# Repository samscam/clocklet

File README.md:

# Clocklet

See also [clocklet.co.uk](https://clocklet.co.uk)

## Overview

This project is the firmware and client apps for clocks made by @samscam including:

### Clocklet
* Custom 17x5 SK9822 LED Matrix display
* Timekeeping: ESP32 (DS3231 as backup)
* Synchronisation: NTP
* Microcontroller: ESP32 Wrover on custom "Clockbrain" board
* Weather source: OpenWeatherMap

### Old Clocklet / Clocky
Earlier prototypes used RGBDigit (WS2812B) 7-segment display and Adafruit Feather Huzzah32.

### Mrs Clockety
* Display: Waveshare epaper 2.9inch https://www.waveshare.com/2.9inch-e-paper-module.htm
* Timekeeping: GPS
* Synchronisation: GPS
* Power management to run from a lipo battery
* Microcontroller: Adafruit Feather Huzzah32

It's all a work in progress.

## Main Features

* Time
* Weather
* Utterances
* Interesing displays and animation
* Ambient light sensing
* Power management (Mrs Clockety)

## Firmware

To build the the firmware:

* Clone the repo **including submodules**
* Install platformio and your editor of choice - I'm using vscode.
* Open up the firmware from the `Embedded` directory
* Pick the *correct environment* for the device you want to build for (by setting it in the first line of `platformio.ini` or by invoking tasks for the specific environment in the editor/cli) this will probably be `clockbrain`
* Plug the device in to your machine over USB
* Check that the device is available to your system... on MacOS it's normally `/dev/cu.SLAB_USBtoUART`
* Build and upload (platformio should download the dependencies if it hasn't done so already)
* Note that API keys are encrypted with gitcrypt

## Seeing the logs (without installing anything much)

You can connect to the clocklet's serial port from a computer with various tools (like screen, miniterm or putty) and see the Clocklet logging.

The important thing to note is that the baud rate of the serial connection is `115200`.

The Clocklet serial port on Mac and Linux will be available as something like `/dev/cu.SLAB_USBtoUART` - you can do an `ls /dev/cu.*` before and after plugging it in to eliminate possibilities.

Then open it up in your tool of choice:
`screen /dev/cu.SLAB_USBtoUART 115200`
`miniterm.py /dev/cu.SLAB_USBtoUART 115200`

## Manually updating firmware (with minimal installing)

1) Install `esptool`

On MacOS this can be done with homebrew: `brew install esptool`
On Linuxes it's probably available from `apt install esptool` or whatever package manager you're using.

2) Download the bin file of the firmware image you want from the releases section on here.

3) Plug in the Clocklet and figure out which port it is on - probably something like `/dev/cu.SLAB_USBtoUART` (that's what we'll use here but replace with whatever it is on your system)

4) Erase the flash (including settings)
`esptool.py -b 115200 -p /dev/cu.SLAB_USBtoUART erase_region 0x9000 0xFF7000`

5) Flash the new firmware image:

`esptool.py -b 115200 -p /dev/cu.SLAB_USBtoUART write_flash 0x10000 clockbrain.bin`

While we are here you can also use esptool to just erase settings (equivalent of doing a factory reset from the app): 
`esptool.py -b 115200 -p /dev/cu.SLAB_USBtoUART erase_region 0x9000 0x5000`

## Client App (iOS)

*Requires Xcode 16*
To build, open via the workspace rather than the Xcode Project.

Contains an experimental library for gluing CoreBluetooth to Combine and SwiftUI via PropertyWrappers called "CombineBluetooth". This may get spun out into a separate project in the future - but for ease of development right now it's in here.

## To follow

* Android client
* Enclosure design (3d printable)
* Hardware design

## License

This is distributed under the MIT License

    MIT License

    Copyright (c) 2017-2020 Sam Easterby-Smith

    Permission is hereby granted, free of charge, to any person obtaining a copy
    of this software and associated documentation files (the "Software"), to deal
    in the Software without restriction, including without limitation the rights
    to use, copy, modify, merge, publish, distribute, sublicense, and/or sell
    copies of the Software, and to permit persons to whom the Software is
    furnished to do so, subject to the following conditions:

    The above copyright notice and this permission notice shall be included in all
    copies or substantial portions of the Software.

    THE SOFTWARE IS PROVIDED "AS IS", WITHOUT WARRANTY OF ANY KIND, EXPRESS OR
    IMPLIED, INCLUDING BUT NOT LIMITED TO THE WARRANTIES OF MERCHANTABILITY,
    FITNESS FOR A PARTICULAR PURPOSE AND NONINFRINGEMENT. IN NO EVENT SHALL THE
    AUTHORS OR COPYRIGHT HOLDERS BE LIABLE FOR ANY CLAIM, DAMAGES OR OTHER
    LIABILITY, WHETHER IN AN ACTION OF CONTRACT, TORT OR OTHERWISE, ARISING FROM,
    OUT OF OR IN CONNECTION WITH THE SOFTWARE OR THE USE OR OTHER DEALINGS IN THE
    SOFTWARE.

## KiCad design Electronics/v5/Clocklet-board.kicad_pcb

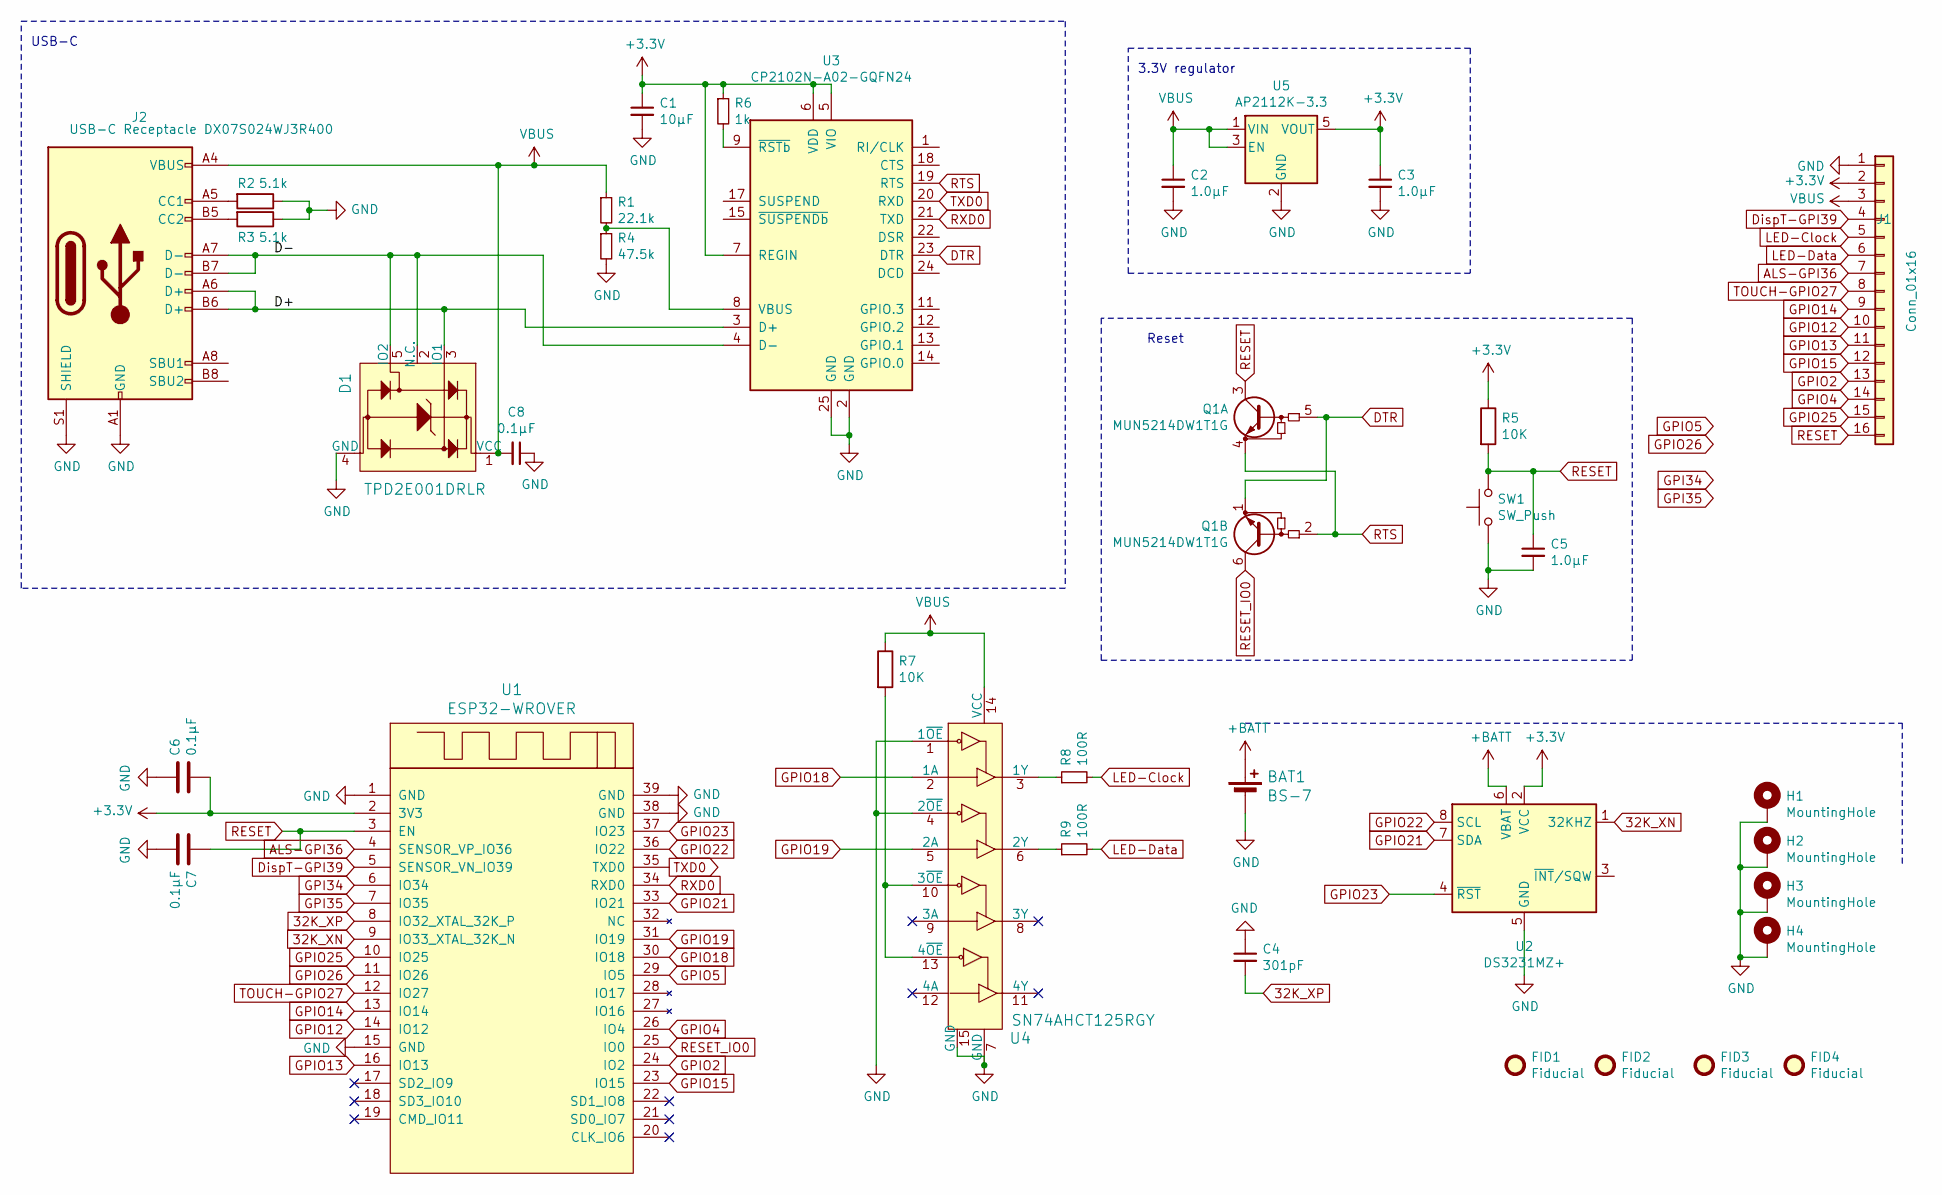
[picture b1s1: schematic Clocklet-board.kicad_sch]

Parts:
BAT1: BS-7; BatteryHolder_Keystone_3000_1x12mm; MPN BS-7; Digi-Key_PN BS-7-ND
C1: 10µF; C_0603_1608Metric; Mouser Ref 80-C0603C106M8PACTU
C2, C3, C5: 1.0µF; C_0603_1608Metric; Mouser Ref 80-C0603C105K4PLR
C4: 301pF; C_0603_1608Metric; Mouser Ref 80-C0603C301J8HACTU
C6, C7, C8: 0.1µF; C_0603_1608Metric; Mouser Ref 710-885012206071
D1: TPD2E001DRLR; SOT-553; MPN TPD2E001DRLR; Digi-Key_PN 296-21883-1-ND
FID1, FID2, FID3, FID4: Fiducial; Fiducial_0.5mm_Mask1mm
H1: MountingHole; MountingHole_2.7mm_M2.5_Pad_Via
H2, H3, H4: MountingHole; MountingHole_2.5mm_Pad_Via
J1: Conn_01x16; PinHeader_1x16_P2.54mm_Vertical
J2: USB-C Receptacle DX07S024WJ3R400; USB-C_Female_Vert_DX07S024WJ3R400-Corrected; Mouser Ref 656-DX07S0024WJ3R400
Q1: MUN5214DW1T1G; SOT-363_SC-70-6; Mouser Ref 863-MUN5214DW1T1G
R1: 22.1k; R_0603_1608Metric; Mouser Ref 71-CRCW060322K1FKEAC
R2, R3: 5.1k; R_0603_1608Metric; Mouser Ref 71-CRCW06035K10FKEAC
R4: 47.5k; R_0603_1608Metric; Mouser Ref 71-CRCW060347K5FKEAC
R5, R7: 10K; R_0603_1608Metric; Mouser Ref 71-CRCW060310K0FKEAC
R6: 1k; R_0603_1608Metric; Mouser Ref 71-CRCW06031K00FKEAC
R8, R9: 100R; R_0603_1608Metric; Mouser Ref 71-CRCW0603100RFKEAC
SW1: SW_Push; SW_SPST_B3U-1000P; Mouser Ref 653-B3U-1000P
U1: ESP32-WROVER; ESP32-WROVER-B-Recs; Mouser Ref 356-ESP32-WROB(16MB)
U2: DS3231MZ+; SOIC-8_3.9x4.9mm_P1.27mm; Mouser Ref 700-DS3231MZ+
U3: CP2102N-A02-GQFN24; QFN-24-1EP_4x4mm_P0.5mm_EP2.6x2.6mm_ThermalVias; Mouser Ref 634-CP2102NA02GQFN24
U4: SN74AHCT125RGY; Texas_S-PVQFN-N14_ThermalVias; MPN SN74AHCT125N; Digi-Key_PN 296-4655-5-ND
U5: AP2112K-3.3; SOT-23-5; Mouser Ref 621-AP2112K-3.3TRG1

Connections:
32K_XN: U1.9 (IO33_XTAL_32K_N), U2.1 (32KHZ)
32K_XP: C4.2, U1.8 (IO32_XTAL_32K_P)
+3V3: C1.1, C3.1, C6.2, J1.2, R5.1, R6.1, U1.2 (3V3), U2.2 (VCC), U3.5 (VIO), U3.6 (VDD), U3.7 (REGIN), U5.5 (VOUT)
+BATT: BAT1.1 (+), U2.6 (VBAT)
/D+: D1.3 (IO1), J2.A6 (D+), J2.B6 (D+), U3.3 (D+)
/D-: D1.2 (N.C.), D1.5 (IO2), J2.A7 (D-), J2.B7 (D-), U3.4 (D-)
ALS-GPI36: J1.7, U1.4 (SENSOR_VP_IO36)
DTR: Q1.1 (E1), Q1.5 (B1), U3.23 (DTR)
DispT-GPI39: J1.4, U1.5 (SENSOR_VN_IO39)
GND: BAT1.2 (-), C1.2, C2.2, C3.2, C4.1, C5.2, C6.1, C7.2, C8.1, D1.4 (GND), H1.1, H2.1, H3.1, H4.1, J1.1, J2.A1 (GND), J2.A12 (GND), J2.B1 (GND), J2.B12 (GND), J2.S1 (SHIELD), R2.1, R3.1, R4.2, SW1.1, U1.1 (GND), U1.15 (GND), U1.38 (GND), U1.39 (GND), U2.5 (GND), U3.2 (GND), U3.25 (GND), U4.1 (1~OE), U4.4 (2~OE), U4.7 (GND), U4.15 (GND), U5.2 (GND)
GPI34: U1.6 (IO34)
GPI35: U1.7 (IO35)
GPIO2: J1.13, U1.24 (IO2)
GPIO4: J1.14, U1.26 (IO4)
GPIO5: U1.29 (IO5)
GPIO12: J1.10, U1.14 (IO12)
GPIO13: J1.11, U1.16 (IO13)
GPIO14: J1.9, U1.13 (IO14)
GPIO15: J1.12, U1.23 (IO15)
GPIO18: U1.30 (IO18), U4.2 (1A)
GPIO19: U1.31 (IO19), U4.5 (2A)
GPIO21: U1.33 (IO21), U2.7 (SDA)
GPIO22: U1.36 (IO22), U2.8 (SCL)
GPIO23: U1.37 (IO23), U2.4 (~RST)
GPIO25: J1.15, U1.10 (IO25)
GPIO26: U1.11 (IO26)
LED-Clock: J1.5, R8.2
LED-Data: J1.6, R9.2
unnamed: J2.A5 (CC1), R2.2
unnamed: J2.B5 (CC2), R3.2
unnamed: R1.2, R4.1, U3.8 (VBUS)
unnamed: R6.2, U3.9 (~RSTb)
unnamed: R7.2, U4.10 (3~OE), U4.13 (4~OE)
unnamed: R8.1, U4.3 (1Y)
unnamed: R9.1, U4.6 (2Y)
RESET: C5.1, C7.1, J1.16, Q1.3 (C1), R5.2, SW1.2, U1.3 (EN)
RESET_IO0: Q1.6 (C1), U1.25 (IO0)
RTS: Q1.2 (B1), Q1.4 (E1), U3.19 (RTS)
RXD0: U1.34 (RXD0), U3.21 (TXD)
TOUCH-GPIO27: J1.8, U1.12 (IO27)
TXD0: U1.35 (TXD0), U3.20 (RXD)
VBUS: C2.1, C8.2, D1.1 (VCC), J1.3, J2.A4 (VBUS), J2.A9 (VBUS), J2.B4 (VBUS), J2.B9 (VBUS), R1.1, R7.1, U4.14 (VCC), U5.1 (VIN), U5.3 (EN)

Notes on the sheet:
3.3V regulator
Reset
USB-C

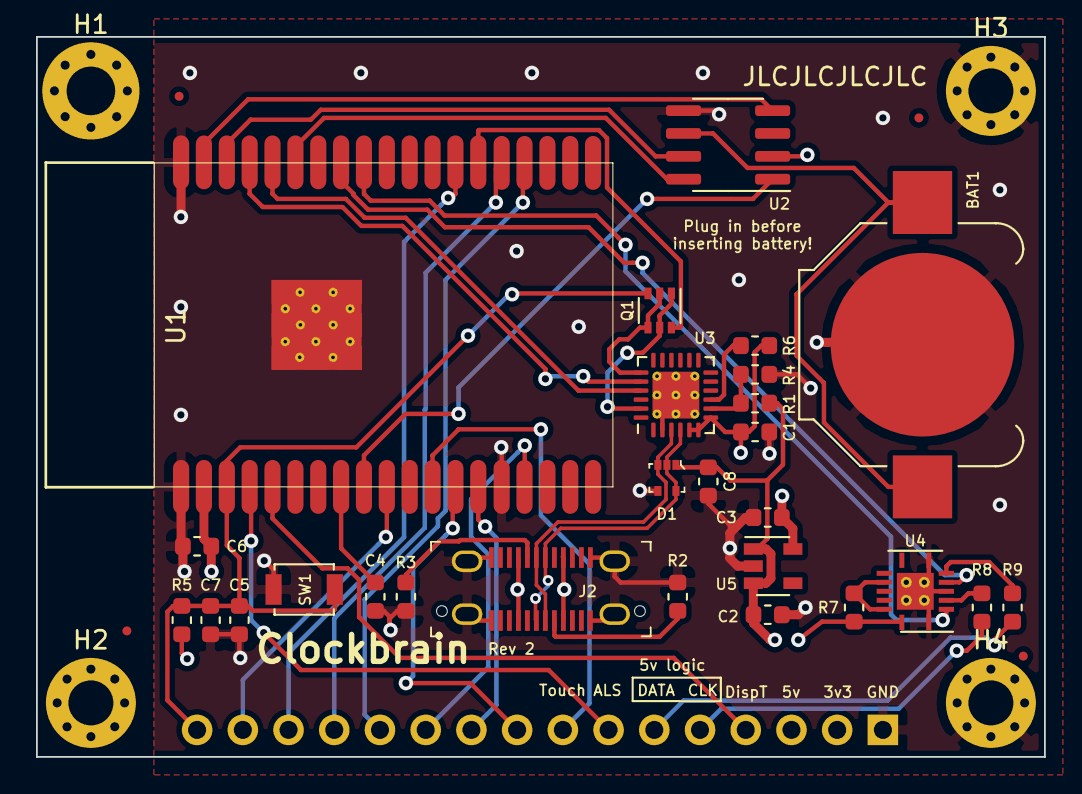
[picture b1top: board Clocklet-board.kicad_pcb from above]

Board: 4 copper layers, 56.0 x 40.0 mm, 36 parts (1 on the bottom side), 38 nets.

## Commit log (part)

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2020-07-11 Force reconnect attempt before running network calls
2020-07-11 Perform a network scan once, on creation of the BTNetworkService
2020-07-11 Adjusted some logging
2020-07-11 Set the partition table for new clocklets
2020-07-11 Only perform network scan on connect rather than at init
2020-07-12 Build both versions at the same time
2020-07-12 Say "WAIT" in capitals
2020-07-14 Matrix - logging using ESP_LOG
2020-07-16 Performed xcode's desired upgrade thing
2020-07-16 Disconnect devices on backgrounding and exit
2020-07-16 Made ConnectionState conform to equatable
2020-07-16 Various visual changes to the main list and detail views
2020-07-17 Just clockbrain while developing
2020-07-17 Added a reset handler to the BTPreferences Service
2020-07-17 Separated BT location service
2020-07-19 Bluetooth advertising - manufacturer data contains hwrev, case colour, serial
2020-07-20 Verbose logging corrections
2020-07-20 Pass locationManager to bluestuff on feathers
2020-07-20 Add a tiny delay between update jobs
2020-07-23 Updated dates and name in LICENSE
2020-07-23 No, don't free the bluetooth device name or you end up with garbage
2020-07-23 Added "configured" property to current location json structure
2020-07-23 Some stylistic movement of char *
2020-07-23 Removed some logging
2020-07-23 Faster startup. Run bluetooth setup sooner and synchronously on core 1
2020-07-24 Corrected some logging in the network status changes
2020-07-24 Inconsequential syntax changes
2020-07-24 Prevent landscape orientation
2020-07-24 Added ability to switch time styles
2020-07-25 Switched back to a viewmodel for networkSummaryView
2020-07-25 Whole bunch of stuff to make CombineBluetooth a bit tidier
2020-07-25 Started tightening up some of the internals of CombineBluetooth
2020-07-25 Removed logging
2020-07-25 Fixed misreporting of pref values over bluetooth
2020-07-26 Changed default value for timeStyle
2020-07-27 Expose bluetooth state to user in the clocklist if it's not right
2020-07-27 Overhaul of how CombineBluetooth conforms to ObservableObject - mostly to support mocking
2020-07-27 Some further layout improvements
2020-07-27 Disable location proxy after one result (because the documentation lies)
2020-07-28 Autoversioning wasn't applied right
2020-07-29 Added gold case colour as number 6
2020-07-29 Added NSBluetoothAlwaysUsageDescription
2020-07-29 Hide the not-got-a-clocklet button if you've got a clocklet
2020-07-30 Boolean (as one byte) characteristics
2020-07-30 Toggle for staging mode
2020-07-30 Improved negative space and layout
2020-07-30 Disabled autocorrection and autocapitalization in the password text field
2020-07-30 Show the git hash in the version info (on serial and over bluetooth)
2020-07-30 Wifi scan characteristic delivers results one-at-a-time
2020-07-31 Put the update scheduler on core 1 - hopefully more reliable
2020-07-31 Disable firmware updates if switched off in preferences
2020-07-31 Removed unused task machinery from BlueStuff
2020-08-01 Remove "wonky" time style from mock clock
2020-08-01 Added rough LocationDetailsView
2020-08-01 Rainbow logging ESP style
2020-08-01 Prep for release 0.0.9
2020-08-01 Significantly upped ram for firmware update response parsing
2020-08-03 Just checking semver stuff
2020-08-03 Sed recipe for getting versions including betas from git
2020-08-03 Brains, brains
2020-08-04 Removed SSL cert verification from Darksky because it was running out of ram and causing problems
2020-08-04 Removed code for adding a custom Generic Attribute Service 0x1801 because it was making things worse
2020-08-04 Switch on notifications within the network service when needed
2020-08-04 Force refresh of advertising data after a disconnect
2020-08-04 Renamed CurrentLocation to ClockLocation
2020-08-04 Moved TechnicalService to the start of the list - because it's less likely to change than the others now
2020-08-05 TIME ZONES
2020-08-05 Removed the periodic force-reconnect when bluetooth is connected but not scanning
2020-08-05 Whitespace
2020-08-06 Default timezone as Europe/London
2020-08-06 Half-implemented partial reset
2020-08-06 Added BluetoothOverlayView for when bluetooth is off or unauthorised or whatever
2020-08-06 LocationDetails has some more sample places including ones with funny timezones
2020-08-06 Always white text on the RoundyButtons
2020-08-06 Info.plist changes
2020-08-11 Corrected bluetooth start/stop for feather-based clocklets
2020-08-11 Better decimal time and blue status shown on display
2020-08-11 Empty virtual function for decimal time not breaking on rgbdigit
2020-08-11 Added releasse notes
2020-08-11 Gradually bumping the number on the efuse
2020-08-16 Case insensitive thunder for darksky
2020-08-16 Minor additions to deployment procedure
2020-08-17 Allow connections to open networks
2020-08-23 Brightness glue is now a float
2020-08-23 Re-enabled snow
2020-08-24 joinNetwork() method doesn't need to throw
2020-08-24 Upped max and min brightness for matrix display
2020-08-26 Colour correction
2020-08-26 Removed unused fetching of serial number
2020-08-26 Supress utterances while connected over bluetooth
2020-08-26 Added brightness setting
2020-08-30 Added autoBrightness toggle
2020-08-30 Yet another attempt at sorting out BLE advertising
2020-08-30 Fall back to ios13 style map - because it works properly
2020-08-30 Show a little message if the brightness setting is missing
2020-08-30 Slight code cleanup
2020-08-31 Added MapKit and CoreLocation into the project frameworks list
2020-09-01 Inconsequential change
2020-09-02 Catch unknown wifi statuses
2020-09-02 Added nimble-arduino
2020-09-03 nimble-arduino v1.0.1
2020-09-04 Made isValidLocation a method rather than a loose function
2020-09-04 Enable blutooth at boot on feathers!
2020-09-04 Fix sticky autoBrightness switch
2020-09-08 A bit of love for RGBDigit
2020-09-08 Moved submodules
2020-09-08 Say that it requires xcode 12
2020-09-08 Refactored Location to ClockLocation to avoid collision with SolTrack
2020-09-08 Return platformio settings to what they should be
2020-09-08 Efuse for clocklet 12
2020-09-08 Rainbows: Corrected troubles with not being near the prime meridian
2020-09-08 Force the app version to be 1.0 to avoid testflight reviews
    Fixes #36
2020-09-09 Removed telltale
    Closes #37
2020-09-09 Removed forcing of rainbows
2020-09-09 Second try at autoassign automation
2020-09-10 Fixed obviously mangled logging when ip address is updated
2020-09-12 Fixed mangled logging on discovering access points #48
2020-09-12 Do not include hidden SSIDs in scan results #50
2020-09-12 Some protection for over-subscription to scan and networkstatus #48
2020-09-12 Removed unused "Credentials.h"
2020-09-12 Corrected url in the board definition file
2020-09-12 Longer delay between wifi scans
2020-09-12 Adjusted heading styles in readme
2020-09-13 Dumbass: was passing a null pointer to the networkScanTask
2020-09-13 Both envs for release
2020-09-27 Add alert to confirm factory resets
    Closes #51
2020-09-27 Improved layout and display of network settings
2020-10-01 Indenting
2020-10-01 SPECIAL BOB VERSION
2020-11-30 Oh fun with serial ports
2020-11-30 Messing with shadows on renders
2021-11-14 ini and config changes
2021-11-15 Updated Semver library
2022-02-10 Wildcard serial port for platformio upload/monitor
2022-09-18 Project file update
2022-09-18 Details view: refactored to use newer syntax
2022-09-18 Attempt to do certificate pinning
2022-09-18 Fixed broken toggle switches and pickers
2022-10-01 Further modernisation of swiftui syntax
2022-10-01 Some improvements to UI previews
2022-10-01 Added disclosure chevron to ConfigItemView and improved hit area
2022-10-01 Use the SwiftUI Map view instead of MKMapView
2022-10-01 Better scaling of wifi strength to SFSymbols icon
2022-10-01 Revert "Use the SwiftUI Map view instead of MKMapView"
    This reverts commit 00a87dcab63da643c20c2163c2968a3af660afee.
2022-10-01 Removed deprecated animations
2022-10-02 Playing with animations on the searching eye
2022-10-07 Updated libraries, fixed code regressions
2022-10-07 Moved nimble-arduino from submodule to platformio dependency
2022-10-07 Fixed glue tags (again)
2022-10-09 Added api key for OpenWeatherMap
2022-10-09 Blatant obvious fail to allocate memory for a URL
2022-10-09 Switch current weather client to OWM
2022-11-02 Change to use x509 certificate bundle instead of pinning
2022-12-06 Fixed serialising of location and network service bluetooth payloads using std::string
2022-12-06 More detail when logging memory usage
2022-12-06 Create and delete preferences within FirmwareUpdates
2022-12-06 Removed weather summary as it was crashy
2022-12-06 Added ability to test forced firmware update
2022-12-06 Removed sloppy redirect handling as it’s now done by the library
2022-12-06 Fixed the Chatham Island time glitch
2022-12-08 iOS: fixed animation when connecting
2022-12-08 iOS: Fancier buttons
2022-12-08 iOS: factory reset button looked stupid
2022-12-08 iOS: Slightly larger icons for configItems
2022-12-09 iOS: Removed unnecessary logging when doing data conversions
2022-12-09 iOS: Renamed ClockConfigurator to ClockConfiguratorView
2022-12-09 iOS: Oh my! No more AppDelegate
2022-12-09 Embedded: only fetch ONE result when getting staging updates
2022-12-10 Embedded: further fixing of snow and drizzle
2022-12-10 Embedded: Added drizzle to display tests
2022-12-10 Embedded: Brought back frost
2022-12-10 Embedded: Moved all the Matrix display files into a directory together
2022-12-16 Embedded: Weird fun with memory leaks
2022-12-16 Embedded: Less new and delete when constructing httpclients
2022-12-17 Embedded: Added force update to gatt - when changing bluetooth services/chars
2022-12-20 Embedded: Changed matrix display to use precip intensity rather than probability
2022-12-20 iOS: Tidied up changes in Characteristic.swift
2022-12-20 Embedded: God mode service
2022-12-28 iOS: Reworked ClockList and root navigation
2022-12-30 iOS: Some refactoring of Bluetooth Overlay … kinda fixes #47 but still could be better
2022-12-30 Embedded: Changed bluetooth callbacks to try negotiating MTU
2022-12-30 Embedded: Removed some unused defines
2022-12-31 Embedded: Removed a leaky leaky leak
2022-12-31 Embedded: Added content length capture in weather parsing (but not actually used it)
2022-12-31 Embedded: Memory tuning for feather
2022-12-31 Embedded: Slight tidy up to order of things in main
2022-12-31 Embedded: Better tuned nimble stack size
2023-01-01 Embedded: Added several more symbols to the matrix font
2023-01-01 Embedded: Firmware updates don’t retry if they fail for a sensible reason (like there is no binary)
2023-01-01 Overhaul of rain/sleet/snow/drizzle
2023-01-02 Embedded: Some further efficiency for drizzle scaling
2023-06-27 Looks like I added a new mac target and forgot
2023-06-27 Refactored `discoverConnections` slightly
2023-06-27 Whitespace change to bump the build number because weird upload failure
2024-07-08 To build in xcode 15.4
2024-07-08 Bumped lots of things to newer versions
2024-07-08 CombineBluetooth min macos is 13.0
2025-04-02 Fixed client app not being able to handle unexpected wifi encryption types (WPA3)
    Closes #55
2025-04-02 Add a spacer to fix misalignment of NetworkDetails section
2025-04-02 Updated readme
    The weather source has been OpenWeatherMap for ages. I fixed the glitches on the small clocks. Apt is not apt-get for most people these days. Xcode is up to version 16.
2025-04-02 Further disabling of autoversioning
2025-04-02 Put back CFBundleShortVersionString and CFBundleVersion from Info.plist but with values in them
2025-04-06 Bunged much electronics design stuff in the repo. It's a mess.
2025-05-11 Added files for the website
2026-03-27 Some rework of ClockDetailsView
2026-04-01 Re-jiggered navigation for iOS26
